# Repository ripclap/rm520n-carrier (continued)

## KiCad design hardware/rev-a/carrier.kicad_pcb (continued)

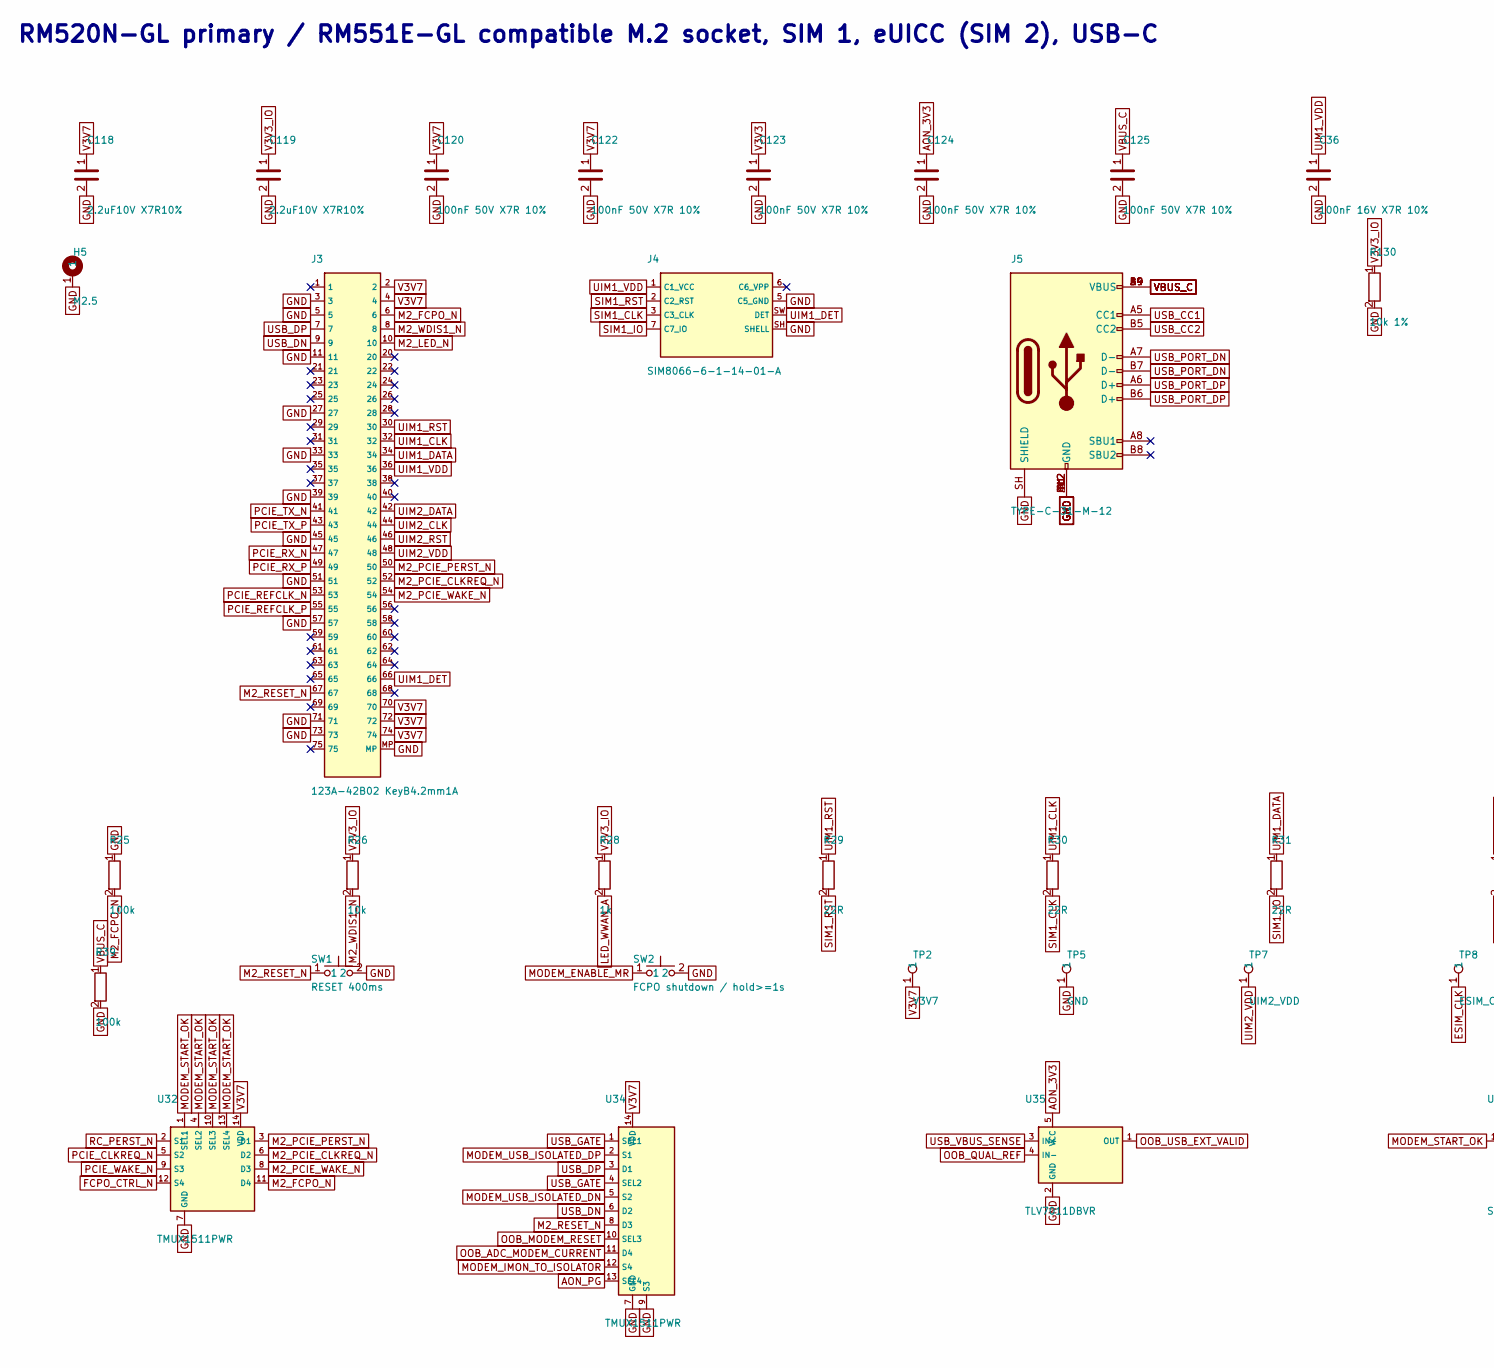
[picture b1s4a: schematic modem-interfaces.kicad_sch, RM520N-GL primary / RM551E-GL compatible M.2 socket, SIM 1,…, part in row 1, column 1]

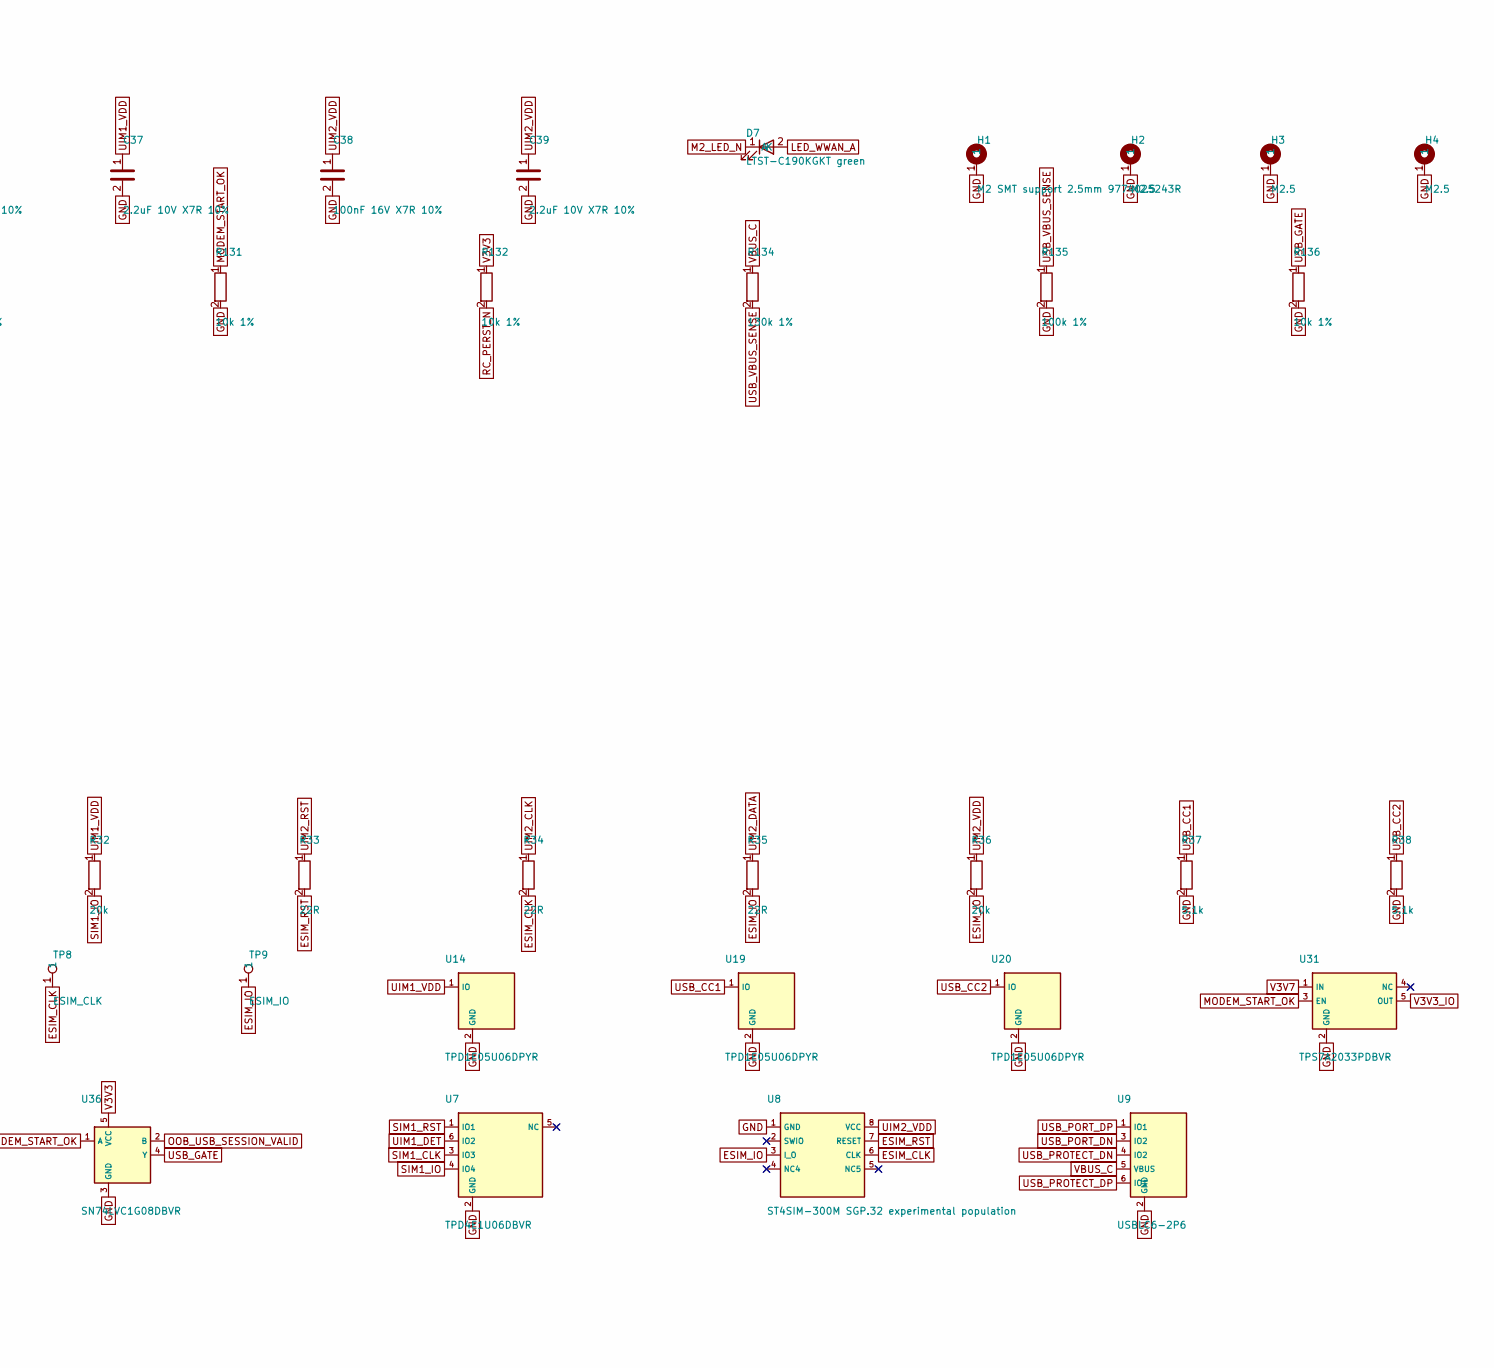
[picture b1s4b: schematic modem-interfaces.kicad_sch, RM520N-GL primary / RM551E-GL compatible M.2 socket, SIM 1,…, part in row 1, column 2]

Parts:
C36, C38: 100nF 16V X7R 10%; C_0402_1005Metric; MPN GRM155R71C104KA88D
C37, C39: 2.2uF 10V X7R 10%; C_0603_1608Metric; MPN CL10B225KP8NNNC
C118, C119: 2.2uF10V X7R10%; C_0603_1608Metric; MPN CL10B225KP8NNNC; LCSC C100082
C120: 100nF 50V X7R 10%; RevA_Dense100_50_C120; MPN CL05B104KB5NNNC; LCSC C960916
C122, C123, C124, C125: 100nF 50V X7R 10%; C_0402_1005Metric; MPN CL05B104KB5NNNC; LCSC C960916
D7: LTST-C190KGKT green; LED_0603_1608Metric; MPN LTST-C190KGKT
H1: M2 SMT support 2.5mm 9774025243R; Wurth_9774025243R_M2_H2p5; MPN 9774025243R
H2, H3, H4, H5: M2.5; MountingHole_2p7_M2p5_GND_SingleBore
J3: 123A-42B02 KeyB4.2mm1A; M2_ATTEND_123A_42B02_CardMinusY; MPN 123A-42B02
J4: SIM8066-6-1-14-01-A; nanoSIM_GCT_SIM8066-6-1-14-01-A_RevB; MPN SIM8066-6-1-14-01-A
J5: TYPE-C-31-M-12; USB_C_HRO_TYPE-C-31-M-12_20201208; MPN TYPE-C-31-M-12
R25, R39: 100k; R_0402_1005Metric; MPN CRCW0402100KFKED
R26: 10k; R_0402_1005Metric; MPN CRCW040210K0FKED
R28: 1k; R_0402_1005Metric; MPN CRCW04021K00FKED
R29, R30, R31, R33, R35: 22R; R_0402_1005Metric; MPN CRCW040222R0FKED
R32, R36: 20k; R_0402_1005Metric; MPN CRCW040220K0FKED
R34: 22R; R_0402_1005Metric_DenseRevA_R34; MPN CRCW040222R0FKED
R37, R38: 5.1k; R_0402_1005Metric; MPN CRCW04025K10FKED
R130, R131, R132, R136: 10k 1%; R_0402_1005Metric; MPN CRCW040210K0FKED
R134: 130k 1%; R_0402_1005Metric; MPN RC0402FR-07130KL; LCSC C93946
R135: 100k 1%; R_0402_1005Metric; MPN CRCW0402100KFKED
SW1: RESET 400ms; SW_SPST_B3U-1000P; MPN B3U-1000P
SW2: FCPO shutdown / hold>=1s; SW_SPST_B3U-1000P; MPN B3U-1000P
TP2: V3V7; TestPoint_Pad_D1.0mm
TP5: GND; TestPoint_Pad_D1.0mm
TP7: UIM2_VDD; TestPoint_Pad_D1.0mm
TP8: ESIM_CLK; TestPoint_Pad_D1.0mm_DenseRevA_TP8
TP9: ESIM_IO; TestPoint_Pad_D1.0mm
U7: TPD4E1U06DBVR; SOT-23-6; MPN TPD4E1U06DBVR
U8: ST4SIM-300M SGP.32 experimental population; ST_ST4SI3M004600HFW_MFF2_ETSI; MPN ST4SI3M004600HFW
U9: USBLC6-2P6; USBLC6-2P6_ST_SOT666; MPN USBLC6-2P6; LCSC C15999
U14, U19, U20: TPD1E05U06DPYR; Texas_DPY0002A_0.6x1mm_P0.65mm; MPN TPD1E05U06DPYR
U31: TPS7A2033PDBVR; SOT-23-5; MPN TPS7A2033PDBVR
U32, U34: TMUX1511PWR; TSSOP-14_4.4x5mm_P0.65mm; MPN TMUX1511PWR
U35: TLV7011DBVR; SOT-23-5; MPN TLV7011DBVR
U36: SN74LVC1G08DBVR; SOT-23-5; MPN SN74LVC1G08DBVR

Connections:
AON_3V3: C124.1, U35.5 (VCC); also elsewhere on the board
AON_PG: U34.13 (SEL4); also elsewhere on the board
ESIM_CLK: R34.2, TP8.1 (1_1), U8.6 (CLK)
ESIM_IO: R35.2, R36.2, TP9.1 (1_1), U8.3 (I_O)
ESIM_RST: R33.2, U8.7 (RESET)
FCPO_CTRL_N: U32.12 (S4); also elsewhere on the board
GND: C36.2, C37.2, C38.2, C39.2, C118.2, C119.2, C120.2, C122.2, C123.2, C124.2, C125.2, H1.1 (1_1), H2.1 (1_1), H3.1 (1_1), H4.1 (1_1), H5.1 (1_1), J3.3, J3.5, J3.11, J3.27, J3.33, J3.39, J3.45, J3.51, J3.57, J3.71, J3.73, J3.MP, J4.5 (C5_GND), J4.SH (SHELL), J5.A1 (GND), J5.A12 (GND), J5.B1 (GND), J5.B12 (GND), J5.SH (SHIELD), R25.1, R37.2, R38.2, R39.2, R130.2, R131.2, R135.2, R136.2, SW1.2, SW2.2, TP5.1 (1_1), U7.2 (GND), U8.1 (GND), U9.2 (GND), U14.2 (GND), U19.2 (GND), U20.2 (GND), U31.2 (GND), U32.7 (GND), U34.7 (GND), U34.9 (S3), U35.2 (GND), U36.3 (GND); also elsewhere on the board
LED_WWAN_A: D7.2 (A), R28.2
M2_FCPO_N: J3.6, R25.2, U32.11 (D4)
M2_LED_N: D7.1 (K), J3.10
M2_PCIE_CLKREQ_N: J3.52, U32.6 (D2)
M2_PCIE_PERST_N: J3.50, U32.3 (D1)
M2_PCIE_WAKE_N: J3.54, U32.8 (D3)
M2_RESET_N: J3.67, SW1.1, U34.8 (D3)
M2_WDIS1_N: J3.8, R26.2
MODEM_ENABLE_MR: SW2.1; also elsewhere on the board
MODEM_IMON_TO_ISOLATOR: U34.12 (S4); also elsewhere on the board
MODEM_START_OK: R131.1, U31.3 (EN), U32.1 (SEL1), U32.4 (SEL2), U32.10 (SEL3), U32.13 (SEL4), U36.1 (A); also elsewhere on the board
MODEM_USB_ISOLATED_DN: U34.5 (S2); also elsewhere on the board
MODEM_USB_ISOLATED_DP: U34.2 (S1); also elsewhere on the board
OOB_ADC_MODEM_CURRENT: U34.11 (D4); also elsewhere on the board
OOB_MODEM_RESET: U34.10 (SEL3); also elsewhere on the board
OOB_QUAL_REF: U35.4 (IN-); also elsewhere on the board
OOB_USB_EXT_VALID: U35.1 (OUT); also elsewhere on the board
OOB_USB_SESSION_VALID: U36.2 (B); also elsewhere on the board
PCIE_CLKREQ_N: U32.5 (S2); also elsewhere on the board
PCIE_REFCLK_N: J3.53; also elsewhere on the board
PCIE_REFCLK_P: J3.55; also elsewhere on the board
PCIE_RX_N: J3.47; also elsewhere on the board
PCIE_RX_P: J3.49; also elsewhere on the board
PCIE_TX_N: J3.41; also elsewhere on the board
PCIE_TX_P: J3.43; also elsewhere on the board
PCIE_WAKE_N: U32.9 (S3); also elsewhere on the board
RC_PERST_N: R132.2, U32.2 (S1); also elsewhere on the board
SIM1_CLK: J4.3 (C3_CLK), R30.2, U7.3 (IO3)
SIM1_IO: J4.7 (C7_IO), R31.2, R32.2, U7.4 (IO4)
SIM1_RST: J4.2 (C2_RST), R29.2, U7.1 (IO1)
UIM1_CLK: J3.32, R30.1
UIM1_DATA: J3.34, R31.1
UIM1_DET: J3.66, J4.SW (DET), U7.6 (IO2)
UIM1_RST: J3.30, R29.1
UIM1_VDD: C36.1, C37.1, J3.36, J4.1 (C1_VCC), R32.1, U14.1 (IO)
UIM2_CLK: J3.44, R34.1
UIM2_DATA: J3.42, R35.1
UIM2_RST: J3.46, R33.1
UIM2_VDD: C38.1, C39.1, J3.48, R36.1, TP7.1 (1_1), U8.8 (VCC)
USB_CC1: J5.A5 (CC1), R37.1, U19.1 (IO)
USB_CC2: J5.B5 (CC2), R38.1, U20.1 (IO)
USB_DN: J3.9, U34.6 (D2)
USB_DP: J3.7, U34.3 (D1)
USB_GATE: R136.1, U34.1 (SEL1), U34.4 (SEL2), U36.4 (Y)
USB_PORT_DN: J5.A7 (D-), J5.B7 (D-), U9.3 (IO2)
USB_PORT_DP: J5.A6 (D+), J5.B6 (D+), U9.1 (IO1)
USB_PROTECT_DN: U9.4 (IO2); also elsewhere on the board
USB_PROTECT_DP: U9.6 (IO1); also elsewhere on the board
USB_VBUS_SENSE: R134.2, R135.1, U35.3 (IN+)
V3V3: C123.1, R132.1, U36.5 (VCC); also elsewhere on the board
V3V3_IO: C119.1, R26.1, R28.1, R130.1, U31.5 (OUT); also elsewhere on the board
V3V7: C118.1, C120.1, C122.1, J3.2, J3.4, J3.70, J3.72, J3.74, TP2.1 (1_1), U31.1 (IN), U32.14 (VDD), U34.14 (VDD); also elsewhere on the board
VBUS_C: C125.1, J5.A4 (VBUS), J5.A9 (VBUS), J5.B4 (VBUS), J5.B9 (VBUS), R39.1, R134.1, U9.5 (VBUS)

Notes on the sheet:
RM520N-GL primary / RM551E-GL compatible M.2 socket, SIM 1, eUICC (SIM 2), USB-C

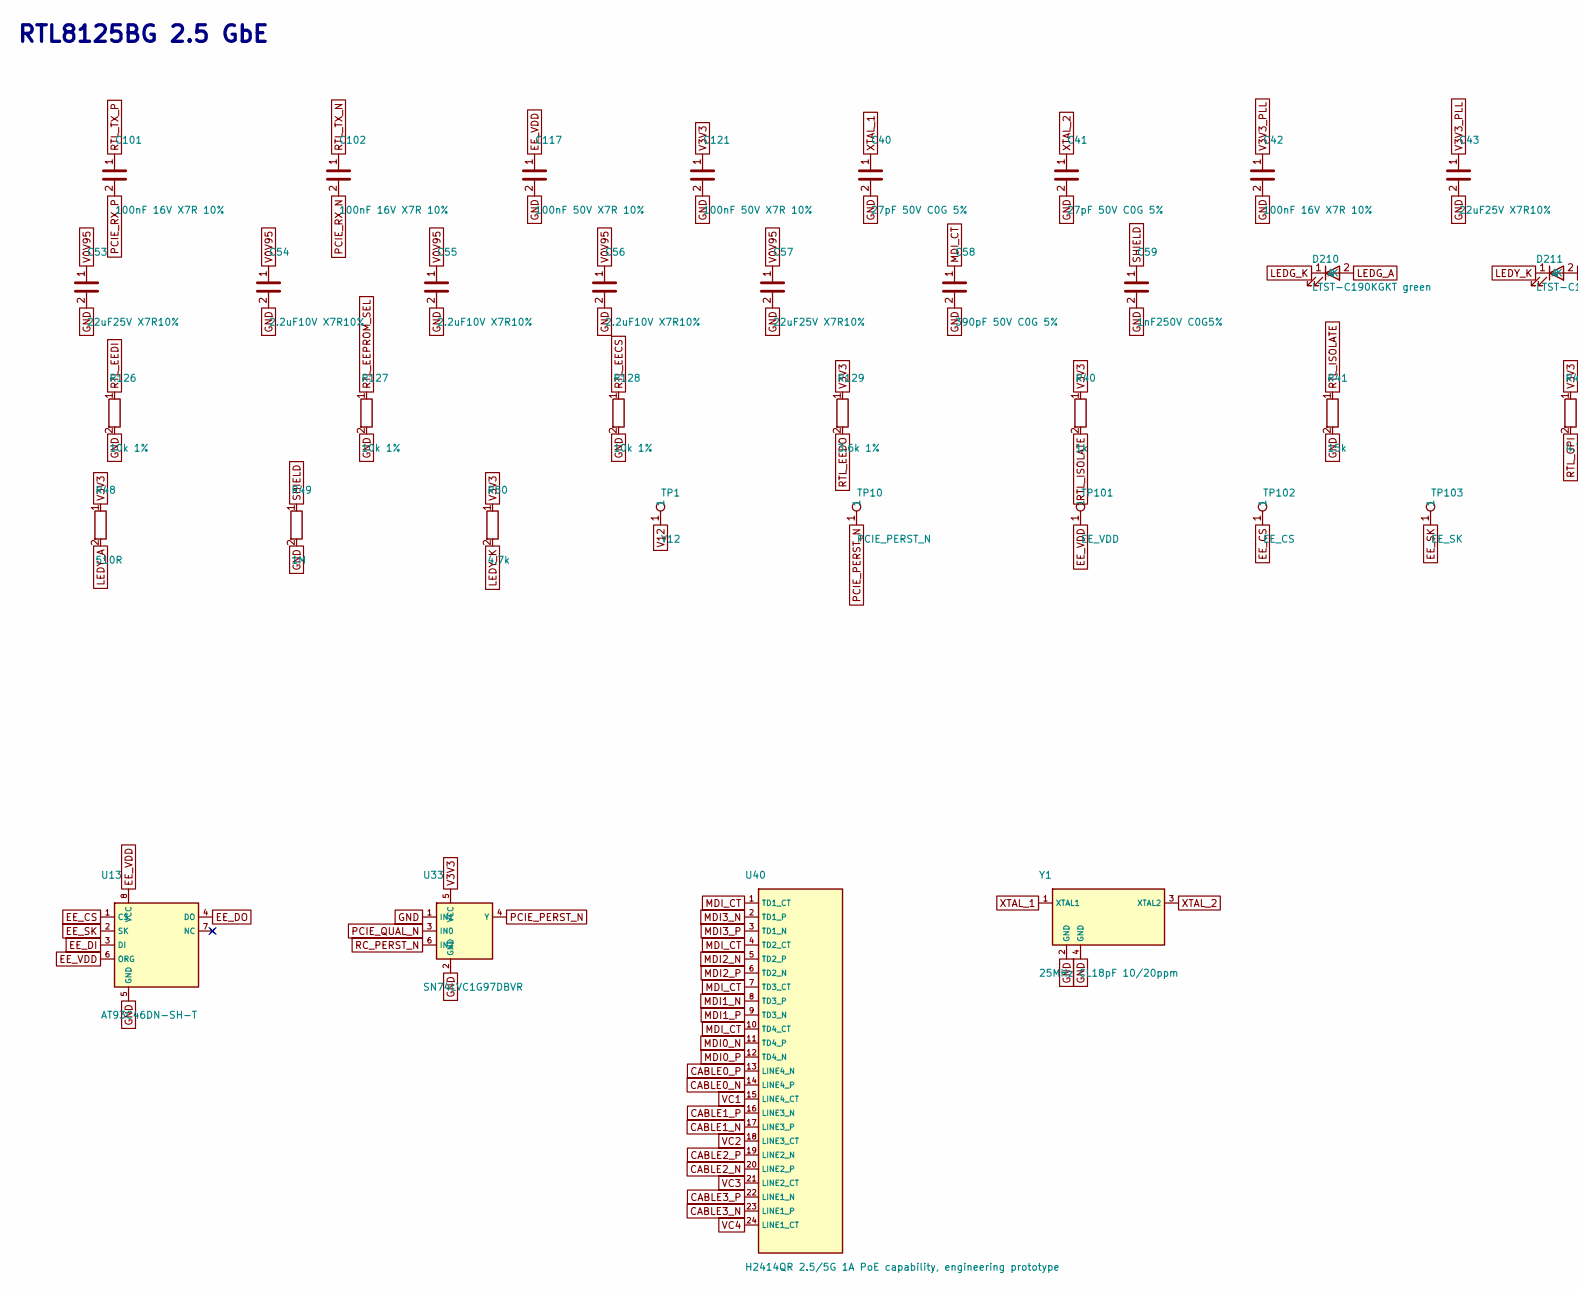
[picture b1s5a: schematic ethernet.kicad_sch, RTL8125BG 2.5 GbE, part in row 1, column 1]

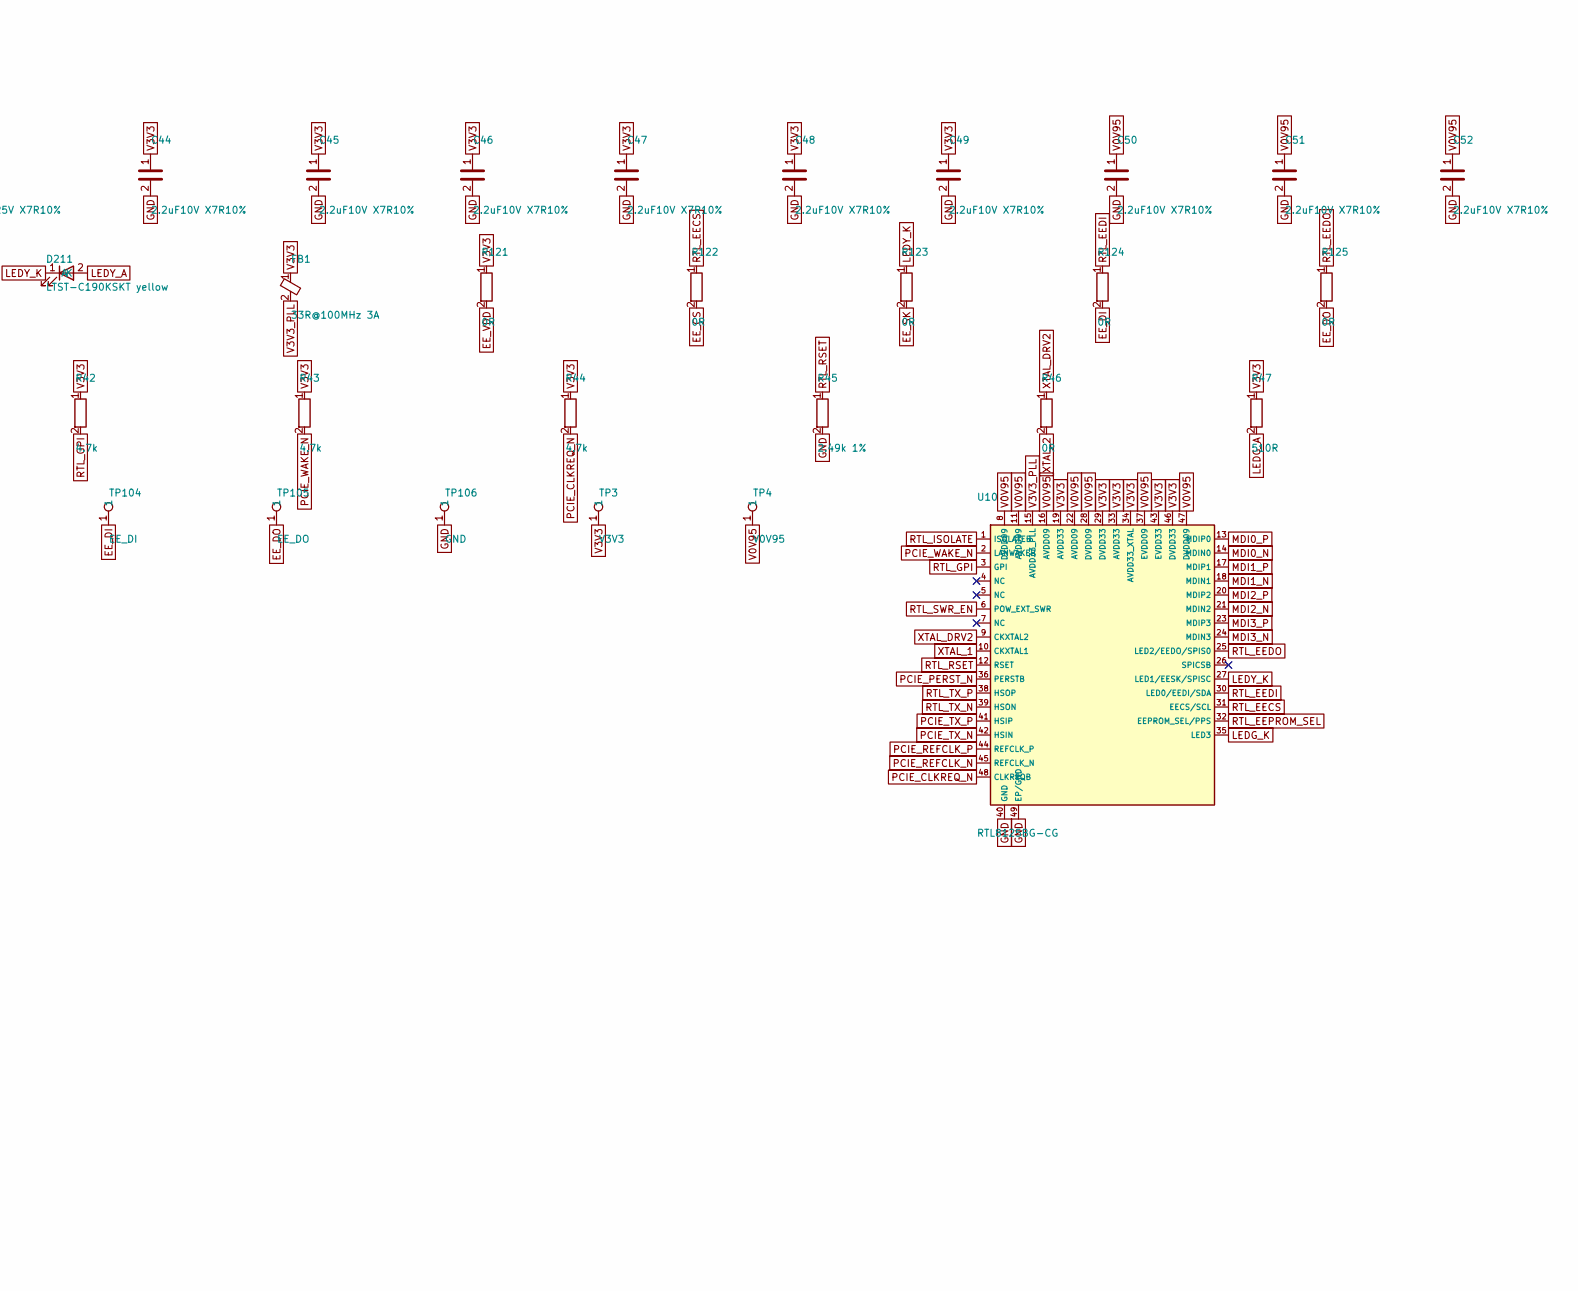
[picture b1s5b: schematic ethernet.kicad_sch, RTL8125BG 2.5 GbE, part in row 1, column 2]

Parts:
C40, C41: 27pF 50V C0G 5%; C_0402_1005Metric; MPN GRM1555C1H270JA01D
C42, C101, C102: 100nF 16V X7R 10%; C_0402_1005Metric; MPN GRM155R71C104KA88D
C43, C53, C57: 22uF25V X7R10%; C_1210_3225Metric; MPN CL32B226KAJNNNE; LCSC C309062
C44, C45, C46, C47, C49, C50, C51, C52, C54, C56: 2.2uF10V X7R10%; C_0603_1608Metric; MPN CL10B225KP8NNNC; LCSC C100082
C48, C55: 2.2uF10V X7R10%; Samsung_CL10_0603_Dense100_50_890; MPN CL10B225KP8NNNC; LCSC C100082
C58: 390pF 50V C0G 5%; C_0402_1005Metric; MPN C0402C391J5GACTU
C59: 1nF250V C0G5%; C_0805_2012Metric; MPN C0805C102JAGACTU
C117, C121: 100nF 50V X7R 10%; C_0402_1005Metric; MPN CL05B104KB5NNNC; LCSC C960916
D210: LTST-C190KGKT green; LED_0603_1608Metric; MPN LTST-C190KGKT
D211: LTST-C190KSKT yellow; LED_0603_1608Metric; MPN LTST-C190KSKT
FB1: 33R@100MHz 3A; L_0603_1608Metric; MPN BLM18PG330SN1D
R40: 1k; R_0402_1005Metric; MPN CRCW04021K00FKED
R41: 15k; R_0402_1005Metric; MPN CRCW040215K0FKED
R42, R43, R44, R50: 4.7k; R_0402_1005Metric; MPN CRCW04024K70FKED
R45: 2.49k 1%; R_0402_1005Metric; MPN CRCW04022K49FKED
R46, R121, R122, R123, R124, R125: 0R; R_0402_1005Metric; MPN CRCW04020000Z0ED
R47, R48: 510R; R_0402_1005Metric; MPN CRCW0402510RFKED
R49: 1M; R_1206_3216Metric; MPN RC1206FR-071ML; LCSC C108083
R126, R127, R128: 10k 1%; R_0402_1005Metric; MPN CRCW040210K0FKED
R129: 3.6k 1%; R_0402_1005Metric; MPN RC0402FR-073K6L; LCSC C137990
TP1: V12; TestPoint_Pad_D1.0mm
TP3: V3V3; TestPoint_Pad_D1.0mm
TP4: V0V95; TestPoint_Pad_D1.0mm
TP10: PCIE_PERST_N; TestPoint_Pad_D1.0mm
TP101: EE_VDD; TestPoint_Pad_D1.0mm
TP102: EE_CS; TestPoint_Pad_D1.0mm
TP103: EE_SK; TestPoint_Pad_D1.0mm
TP104: EE_DI; TestPoint_Pad_D1.0mm
TP105: EE_DO; TestPoint_Pad_D1.0mm
TP106: GND; TestPoint_Pad_D1.0mm
U10: RTL8125BG-CG; TQFN-48_L6.0-W6.0-P0.40-BL-EP4.5_RevA_EP625_890_Heatsink1090; MPN RTL8125BG-CG; LCSC C3013605
U13: AT93C46DN-SH-T; SOIC-8_3.9x4.9mm_P1.27mm; MPN AT93C46DN-SH-T
U33: SN74LVC1G97DBVR; SOT-23-6; MPN SN74LVC1G97DBVR
U40: H2414QR 2.5/5G 1A PoE capability, engineering pro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; ENETTR_H2414QR_24_SMD_Manufacturer; MPN H2414QR; LCSC C4155001
Y1: 25MHz CL18pF 10/20ppm; Crystal_ABM8_Abracon_3.2x2.5; MPN ABM8-25.000MHZ-D1X-T

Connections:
CABLE0_N: U40.14 (LINE4_P); also elsewhere on the board
CABLE0_P: U40.13 (LINE4_N); also elsewhere on the board
CABLE1_N: U40.17 (LINE3_P); also elsewhere on the board
CABLE1_P: U40.16 (LINE3_N); also elsewhere on the board
CABLE2_N: U40.20 (LINE2_P); also elsewhere on the board
CABLE2_P: U40.19 (LINE2_N); also elsewhere on the board
CABLE3_N: U40.23 (LINE1_P); also elsewhere on the board
CABLE3_P: U40.22 (LINE1_N); also elsewhere on the board
EE_CS: R122.2, TP102.1 (1_1), U13.1 (CS)
EE_DI: R124.2, TP104.1 (1_1), U13.3 (DI)
EE_DO: R125.2, TP105.1 (1_1), U13.4 (DO)
EE_SK: R123.2, TP103.1 (1_1), U13.2 (SK)
EE_VDD: C117.1, R121.2, TP101.1 (1_1), U13.6 (ORG), U13.8 (VCC)
GND: C40.2, C41.2, C42.2, C43.2, C44.2, C45.2, C46.2, C47.2, C48.2, C49.2, C50.2, C51.2, C52.2, C53.2, C54.2, C55.2, C56.2, C57.2, C58.2, C59.2, C117.2, C121.2, R41.2, R45.2, R49.2, R126.2, R127.2, R128.2, TP106.1 (1_1), U10.40 (GND), U10.49 (EP/GND), U13.5 (GND), U33.1 (IN1), U33.2 (GND), Y1.2 (GND), Y1.4 (GND); also elsewhere on the board
LEDG_A: D210.2 (A), R47.2
LEDG_K: D210.1 (K), U10.35 (LED3)
LEDY_A: D211.2 (A), R48.2
LEDY_K: D211.1 (K), R50.2, R123.1, U10.27 (LED1/EESK/SPISC)
MDI0_N: U10.14 (MDIN0), U40.11 (TD4_P)
MDI0_P: U10.13 (MDIP0), U40.12 (TD4_N)
MDI1_N: U10.18 (MDIN1), U40.8 (TD3_P)
MDI1_P: U10.17 (MDIP1), U40.9 (TD3_N)
MDI2_N: U10.21 (MDIN2), U40.5 (TD2_P)
MDI2_P: U10.20 (MDIP2), U40.6 (TD2_N)
MDI3_N: U10.24 (MDIN3), U40.2 (TD1_P)
MDI3_P: U10.23 (MDIP3), U40.3 (TD1_N)
MDI_CT: C58.1, U40.1 (TD1_CT), U40.4 (TD2_CT), U40.7 (TD3_CT), U40.10 (TD4_CT)
PCIE_CLKREQ_N: R44.2, U10.48 (CLKREQB); also elsewhere on the board
PCIE_PERST_N: TP10.1 (1_1), U10.36 (PERSTB), U33.4 (Y)
PCIE_QUAL_N: U33.3 (IN0); also elsewhere on the board
PCIE_REFCLK_N: U10.45 (REFCLK_N); also elsewhere on the board
PCIE_REFCLK_P: U10.44 (REFCLK_P); also elsewhere on the board
PCIE_RX_N: C102.2; also elsewhere on the board
PCIE_RX_P: C101.2; also elsewhere on the board
PCIE_TX_N: U10.42 (HSIN); also elsewhere on the board
PCIE_TX_P: U10.41 (HSIP); also elsewhere on the board
PCIE_WAKE_N: R43.2, U10.2 (LANWAKEB); also elsewhere on the board
RC_PERST_N: U33.6 (IN2); also elsewhere on the board
RTL_EECS: R122.1, R128.1, U10.31 (EECS/SCL)
RTL_EEDI: R124.1, R126.1, U10.30 (LED0/EEDI/SDA)
RTL_EEDO: R125.1, R129.2, U10.25 (LED2/EEDO/SPIS0)
RTL_EEPROM_SEL: R127.1, U10.32 (EEPROM_SEL/PPS)
RTL_GPI: R42.2, U10.3 (GPI)
RTL_ISOLATE: R40.2, R41.1, U10.1 (ISOLATEB)
RTL_RSET: R45.1, U10.12 (RSET)
RTL_SWR_EN: U10.6 (POW_EXT_SWR); also elsewhere on the board
RTL_TX_N: C102.1, U10.39 (HSON)
RTL_TX_P: C101.1, U10.38 (HSOP)
SHIELD: C59.1, R49.1; also elsewhere on the board
V0V95: C50.1, C51.1, C52.1, C53.1, C54.1, C55.1, C56.1, C57.1, TP4.1 (1_1), U10.8 (DVDD09), U10.11 (AVDD09), U10.16 (AVDD09), U10.22 (AVDD09), U10.28 (DVDD09), U10.37 (EVDD09), U10.47 (DVDD09); also elsewhere on the board
V3V3: C44.1, C45.1, C46.1, C47.1, C48.1, C49.1, C121.1, FB1.1, R40.1, R42.1, R43.1, R44.1, R47.1, R48.1, R50.1, R121.1, R129.1, TP3.1 (1_1), U10.19 (AVDD33), U10.29 (DVDD33), U10.33 (AVDD33), U10.34 (AVDD33_XTAL), U10.43 (EVDD33), U10.46 (DVDD33), U33.5 (VCC); also elsewhere on the board
V3V3_PLL: C42.1, C43.1, FB1.2, U10.15 (AVDD33_PLL)
V12: TP1.1 (1_1); also elsewhere on the board
VC1: U40.15 (LINE4_CT); also elsewhere on the board
VC2: U40.18 (LINE3_CT); also elsewhere on the board
VC3: U40.21 (LINE2_CT); also elsewhere on the board
VC4: U40.24 (LINE1_CT); also elsewhere on the board
XTAL_1: C40.1, U10.10 (CKXTAL1), Y1.1 (XTAL1)
XTAL_2: C41.1, R46.2, Y1.3 (XTAL2)
XTAL_DRV2: R46.1, U10.9 (CKXTAL2)

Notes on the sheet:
RTL8125BG 2.5 GbE

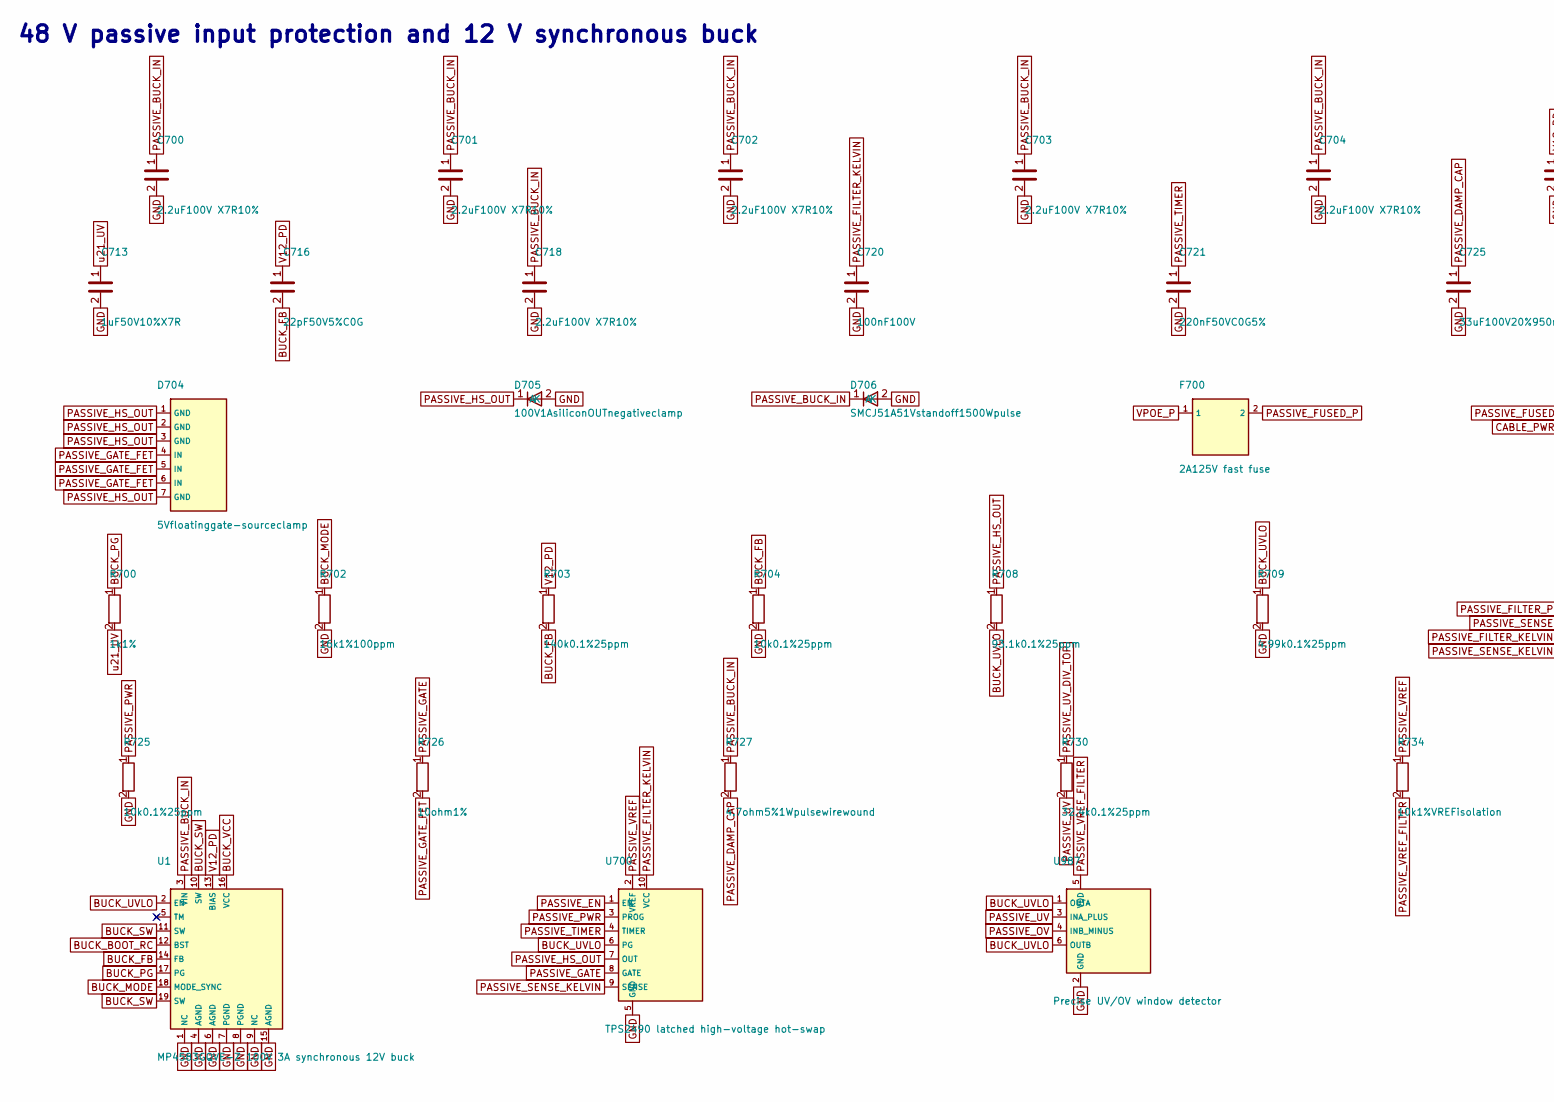
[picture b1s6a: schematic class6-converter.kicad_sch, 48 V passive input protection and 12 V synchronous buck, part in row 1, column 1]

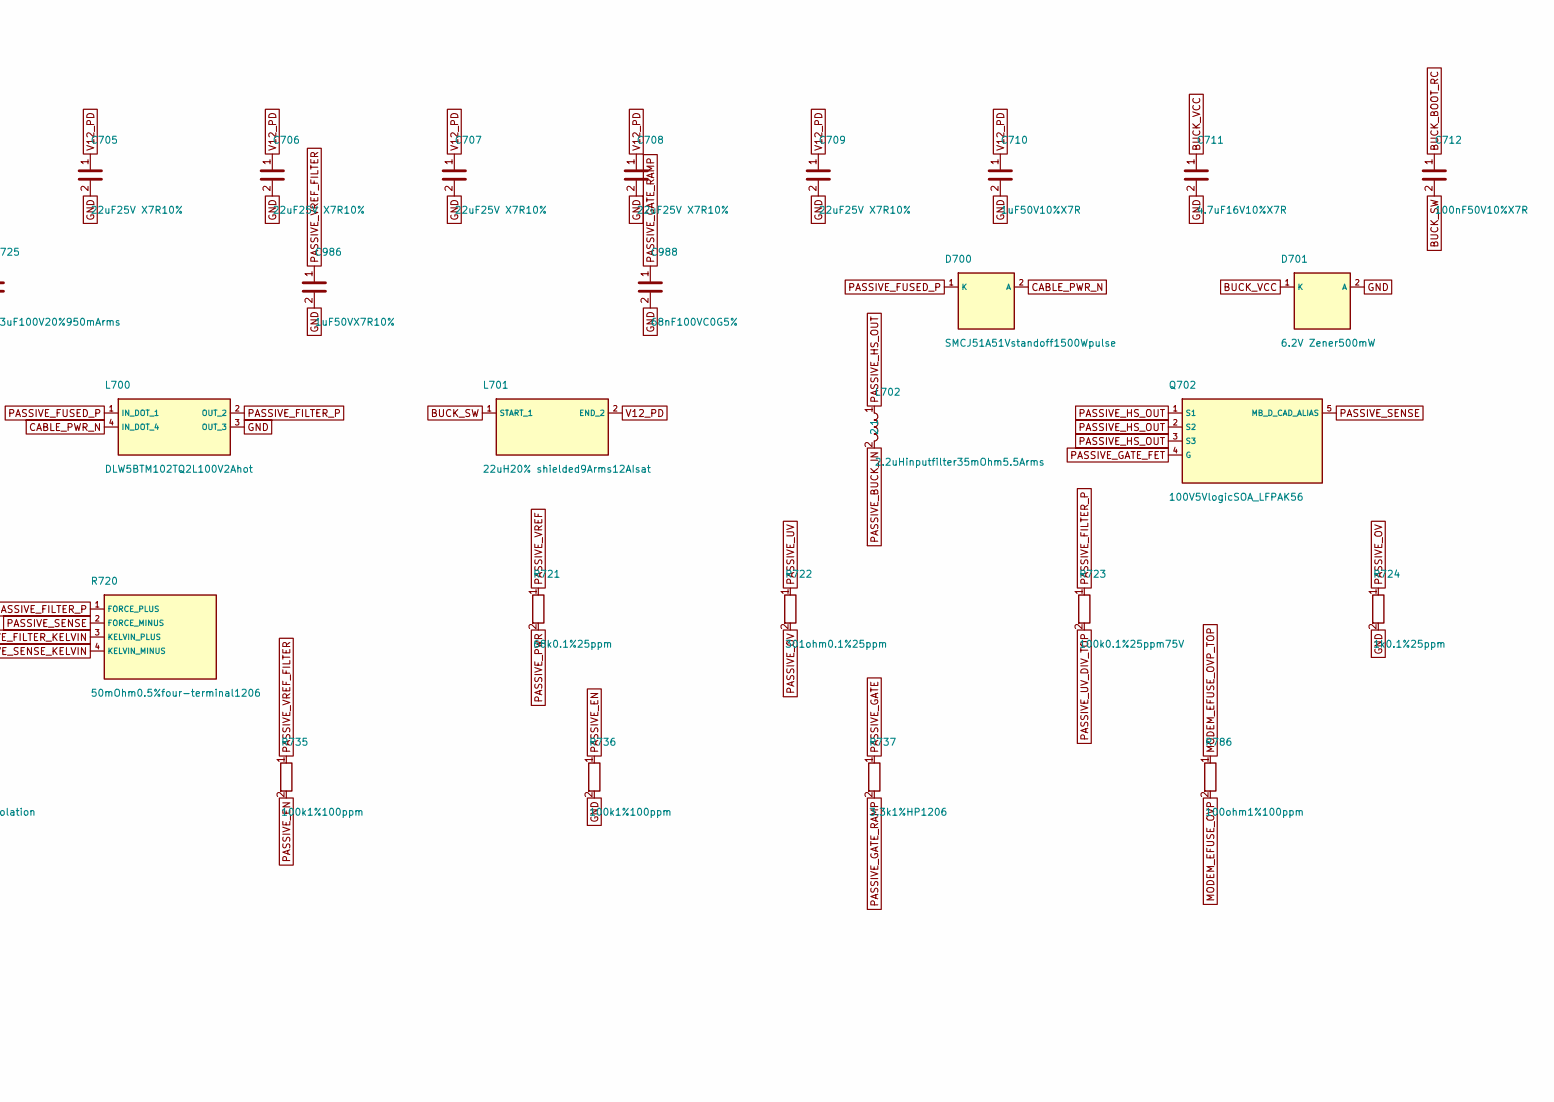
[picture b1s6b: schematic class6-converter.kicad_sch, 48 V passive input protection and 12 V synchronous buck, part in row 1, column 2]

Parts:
C700, C701, C702, C703, C704, C718: 2.2uF100V X7R10%; C_1210_3225Metric; MPN CGA6N3X7R2A225K230AB
C705, C706, C707, C708, C709: 22uF25V X7R10%; C_1210_3225Metric; MPN CL32B226KAJNNNE; LCSC C309062
C710, C713: 1uF50V10%X7R; C_0805_2012Metric; MPN CL21B105KBFNNNF
C711: 4.7uF16V10%X7R; C_0805_2012Metric; MPN C0805C475K4RACTU
C712: 100nF50V10%X7R; C_0402_1005Metric; MPN CL05B104KB5NNNC
C716: 22pF50V5%C0G; C_0402_1005Metric; MPN C0402C220J5GACTU
C720: 100nF100V; C_0603_1608Metric; MPN GRM188R72A104KA35D
C721: 220nF50VC0G5%; C1206; MPN GRM31C5C1H224JE02L
C725: 33uF100V20%950mArms; Nichicon_UHW2A330MPD_Radial_D8_P3.5; MPN UHW2A330MPD
C986: 1uF50VX7R10%; C_0805_2012Metric; MPN CL21B105KBFNNNF; LCSC C16195091
C988: 68nF100VC0G5%; C1206; MPN GRM31C5C2A683JA01L
D700, D706: SMCJ51A51Vstandoff1500Wpulse; D_SMC; MPN SMCJ51A-E3/57T
D701: 6.2V Zener500mW; D_SOD-123; MPN BZT52C6V2-7-F
D704: 5Vfloatinggate-sourceclamp; TI_DRV0006A_TVS0500_PRIMARY; MPN TVS0500DRVR
D705: 100V1AsiliconOUTnegativeclamp; Diodes_S1B_SMA_PRIMARY; MPN S1B-13-F
F700: 2A125V fast fuse; Littelfuse_451_6.1x2.69; MPN 0451002.MRL
L700: DLW5BTM102TQ2L100V2Ahot; Murata_DLW5BTM102TQ2L_4_SMD; MPN DLW5BTM102TQ2L
L701: 22uH20% shielded9Arms12AIsat; BOURNS_SRP1265A_LEAD_FRAME; MPN SRP1265A-220M
L702: 2.2uHinputfilter35mOhm5.5Arms; L_Bourns_SRP5030T; MPN SRP5030TA-2R2M
Q702: 100V5VlogicSOA_LFPAK56; NEXPERIA_LFPAK56_PRIMARY_AUDITED; MPN PSMN015-100YLX
R700: 1k1%; R_0603_1608Metric; MPN RC0603FR-071KL
R702: 16k1%100ppm; R_0603_1608Metric; MPN RC0603FR-0716KL
R703: 140k0.1%25ppm; R_0603_1608Metric; MPN RT0603BRD07140KL
R704, R725: 10k0.1%25ppm; R_0603_1608Metric; MPN RT0603BRD0710KL
R708: 93.1k0.1%25ppm; R_0603_1608Metric; MPN RT0603BRD0793K1L
R709: 4.99k0.1%25ppm; R_0603_1608Metric; MPN RT0603BRD074K99L
R720: 50mOhm0.5%four-terminal1206; Littelfuse_L4CL1206_A_PRIMARY; MPN L4CL1206LR050DNR-A
R721: 68k0.1%25ppm; R_0603_1608Metric; MPN RT0603BRD0768KL
R722: 301ohm0.1%25ppm; R_0402_1005Metric; MPN RT0402BRD07301RL
R723: 100k0.1%25ppm75V; R_0603_1608Metric; MPN TNPW0603100KBEEA
R724: 1k0.1%25ppm; R_0402_1005Metric; MPN RT0402BRD071KL
R726: 10ohm1%; R_0603_1608Metric; MPN RC0603FR-0710RL
R727: 4.7ohm5%1Wpulsewirewound; Vishay_AC01_P17_8_PRIMARY; MPN AC01000004708JA100
R730: 32.4k0.1%25ppm; R_0603_1608Metric; MPN RT0603BRD0732K4L
R734: 10k1%VREFisolation; R_0603_1608Metric; MPN RC0603FR-0710KL
R735, R736: 100k1%100ppm; R_0402_1005Metric; MPN CRCW0402100KFKED
R737: 3.3k1%HP1206; R1206; MPN CRCW12063K30FKEAHP
R786: 100ohm1%100ppm; RevA_Dense100_50_R786; MPN CRCW0402100RFKED
U1: MP4583GQVE-Z 100V 3A synchronous 12V buck; MPS_MP4583_QFN19_3x5_PRIMARY; MPN MP4583GQVE-Z
U700: TPS2490 latched high-voltage hot-swap; TI_DGS0010A_TPS2490_PRIMARY; MPN TPS2490DGSR
U987: Precise UV/OV window detector; TI_DDC0006A_PRIMARY; MPN TPS3700DDCR; LCSC C33002

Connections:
BUCK_BOOT_RC: C712.1, U1.12 (BST)
BUCK_FB: C716.2, R703.2, R704.1, U1.14 (FB)
BUCK_MODE: R702.1, U1.18 (MODE_SYNC)
BUCK_PG: R700.1, U1.17 (PG)
BUCK_SW: C712.2, L701.1 (START_1), U1.10 (SW), U1.11 (SW), U1.19 (SW)
BUCK_UVLO: R708.2, R709.1, U1.2 (EN), U700.6 (PG), U987.1 (OUTA), U987.6 (OUTB)
BUCK_VCC: C711.1, D701.1 (K), U1.16 (VCC)
CABLE_PWR_N: D700.2 (A), L700.4 (IN_DOT_4); also elsewhere on the board
GND: C700.2, C701.2, C702.2, C703.2, C704.2, C705.2, C706.2, C707.2, C708.2, C709.2, C710.2, C711.2, C713.2, C718.2, C720.2, C721.2, C725.2, C986.2, C988.2, D701.2 (A), D705.2 (A), D706.2 (A), L700.3 (OUT_3), R702.2, R704.2, R709.2, R724.2, R725.2, R736.2, U1.1 (NC), U1.4 (AGND), U1.6 (AGND), U1.7 (PGND), U1.8 (PGND), U1.9 (NC), U1.15 (AGND), U700.5 (GND), U987.2 (GND); also elsewhere on the board
MODEM_EFUSE_OVP: R786.2; also elsewhere on the board
MODEM_EFUSE_OVP_TOP: R786.1; also elsewhere on the board
PASSIVE_BUCK_IN: C700.1, C701.1, C702.1, C703.1, C704.1, C718.1, D706.1 (K), L702.2, R727.1, U1.3 (VIN)
PASSIVE_DAMP_CAP: C725.1, R727.2
PASSIVE_EN: R735.2, R736.1, U700.1 (EN)
PASSIVE_FILTER_KELVIN: C720.1, R720.3 (KELVIN_PLUS), U700.10 (VCC)
PASSIVE_FILTER_P: L700.2 (OUT_2), R720.1 (FORCE_PLUS), R723.1
PASSIVE_FUSED_P: D700.1 (K), F700.2, L700.1 (IN_DOT_1)
PASSIVE_GATE: R726.1, R737.1, U700.8 (GATE)
PASSIVE_GATE_FET: D704.4 (IN), D704.5 (IN), D704.6 (IN), Q702.4 (G), R726.2
PASSIVE_GATE_RAMP: C988.1, R737.2
PASSIVE_HS_OUT: D704.1 (GND), D704.2 (GND), D704.3 (GND), D704.7 (GND), D705.1 (K), L702.1, Q702.1 (S1), Q702.2 (S2), Q702.3 (S3), R708.1, U700.7 (OUT)
PASSIVE_OV: R722.2, R724.1, U987.4 (INB_MINUS)
PASSIVE_PWR: R721.2, R725.1, U700.3 (PROG)
PASSIVE_SENSE: Q702.5 (MB_D_CAD_ALIAS), R720.2 (FORCE_MINUS)
PASSIVE_SENSE_KELVIN: R720.4 (KELVIN_MINUS), U700.9 (SENSE)
PASSIVE_TIMER: C721.1, U700.4 (TIMER)
PASSIVE_UV: R722.1, R730.2, U987.3 (INA_PLUS)
PASSIVE_UV_DIV_TOP: R723.2, R730.1
PASSIVE_VREF: R721.1, R734.1, U700.2 (VREF)
PASSIVE_VREF_FILTER: C986.1, R734.2, R735.1, U987.5 (VDD)
V12_PD: C705.1, C706.1, C707.1, C708.1, C709.1, C710.1, C716.1, L701.2 (END_2), R703.1, U1.13 (BIAS); also elsewhere on the board
VPOE_P: F700.1; also elsewhere on the board
u21_UV: C713.1, R700.2; also elsewhere on the board

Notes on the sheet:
48 V passive input protection and 12 V synchronous buck
